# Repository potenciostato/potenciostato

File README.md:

# Potenciostato con comunicación USB sobre LPCXpresso y FreeRTOS

Proyecto Final de la carrera Ingeniería Electrónica de la Universidad Tecnológica Nacional Facultad Regional Avellaneda <br>

El potenciostato es un dispositivo electrónico utilizado en la mayoría de los experimentos electroquímicos.<br>
Es un instrumento capaz de caracterizar la impedancia de una sustancia por medio de la medición de corriente y tensión.<br>

Integrantes del grupo:
- [Arluna, Gustavo Luis](mailto:gustavoarluna@gmail.com)<br>
- [Gómez Caamaño, Axel Lucas](mailto:gomezaxel.lucas@gmail.com)<br>
- [Trinidad, Hernán](mailto:hernantri@gmail.com)<br>

Para más info visitar la [Página Web Oficial](https://potenciostato.github.io) del proyecto

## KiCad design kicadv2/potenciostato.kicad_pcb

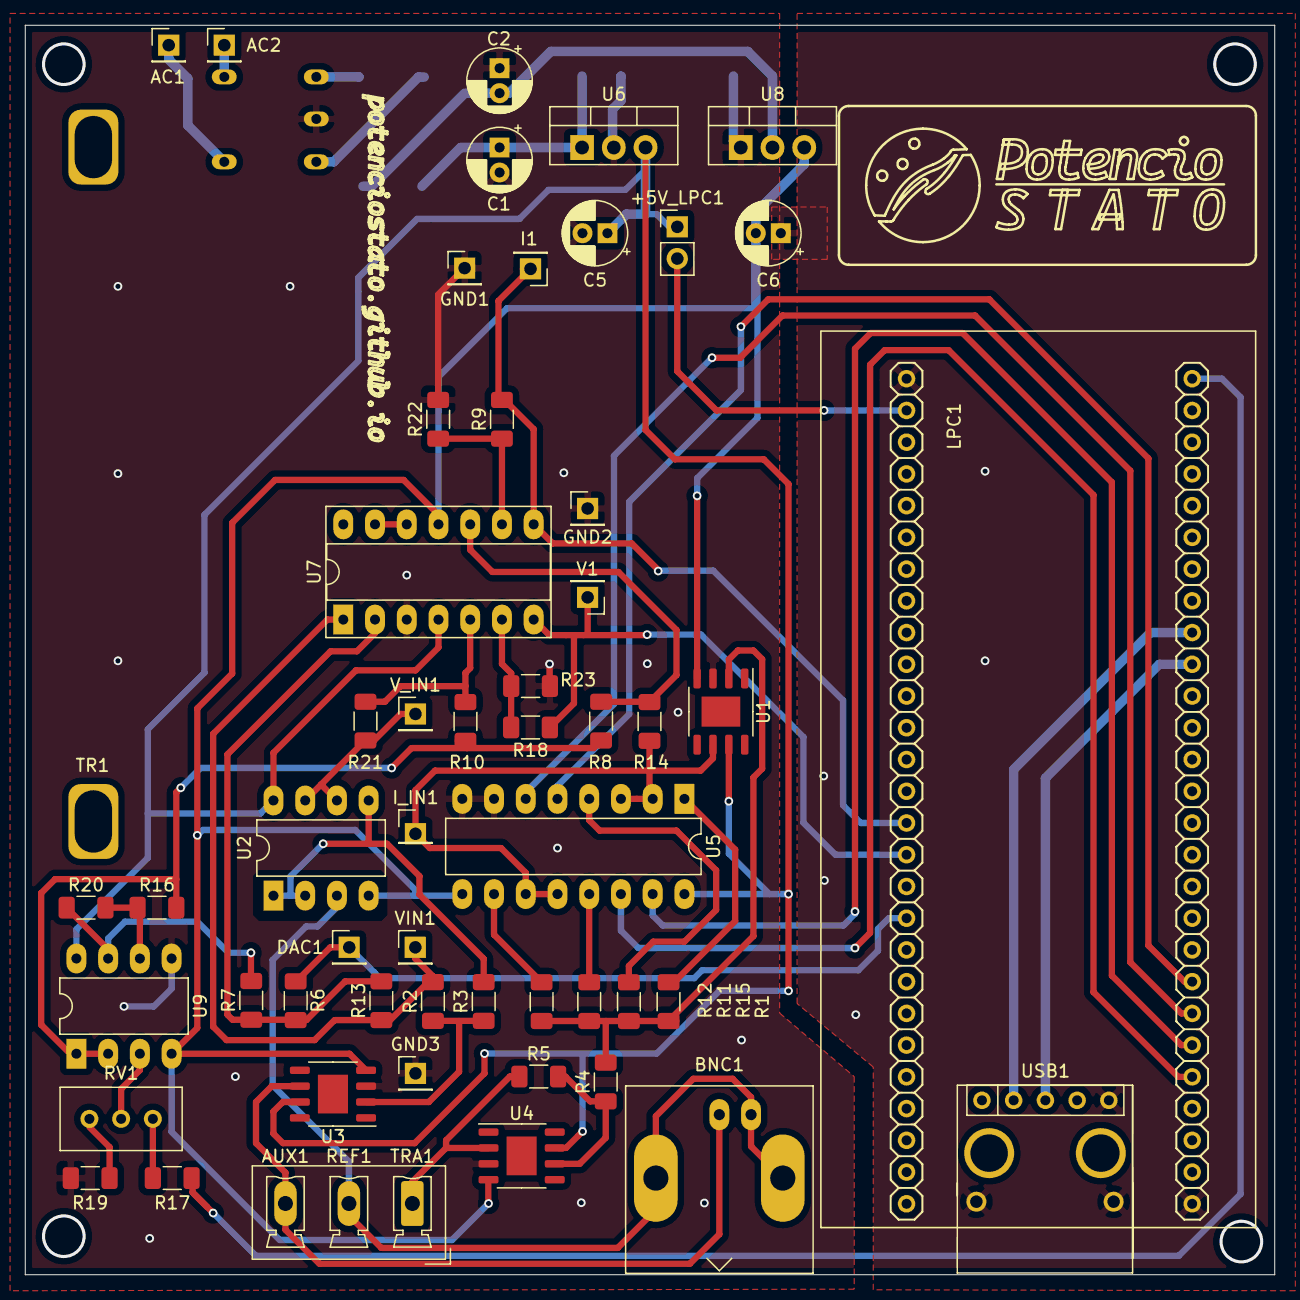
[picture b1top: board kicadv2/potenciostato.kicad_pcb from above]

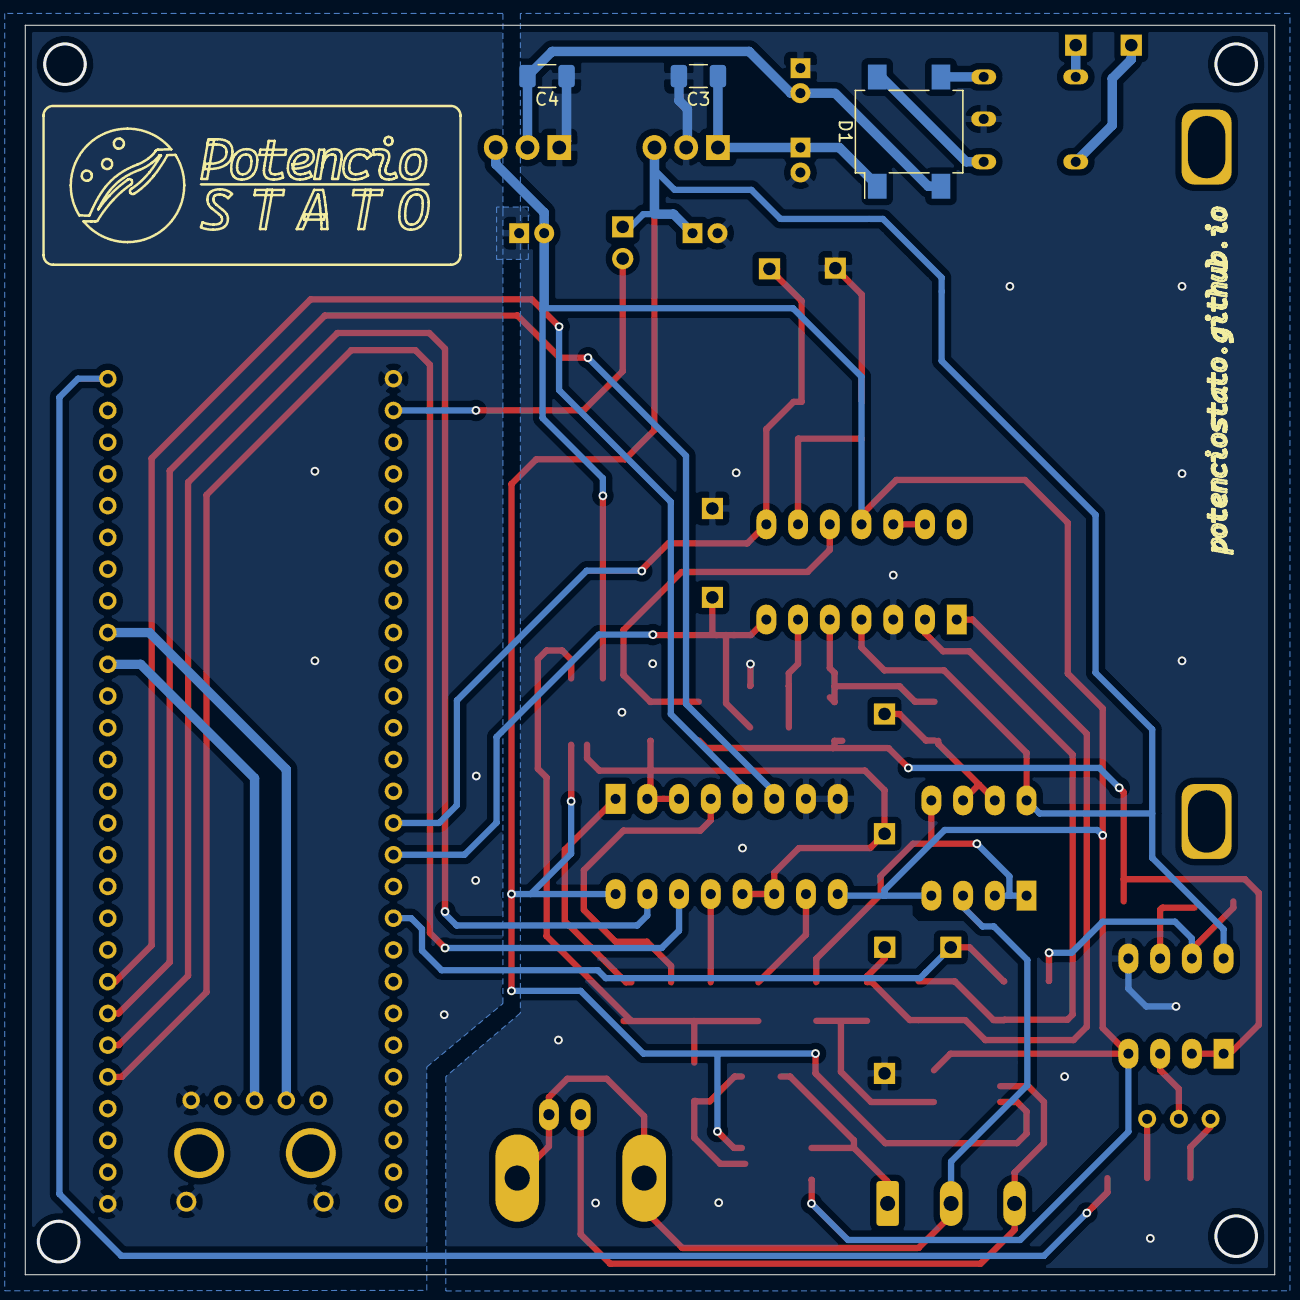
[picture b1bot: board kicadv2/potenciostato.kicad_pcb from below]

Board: 2 copper layers, 100.0 x 100.0 mm, 57 parts (3 on the bottom side), 46 nets.

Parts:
+5V_LPC1: alimentacion_lpc; PinHeader_1x02_P2.54mm_Vertical
AC1: AC1; PinHeader_1x01_P2.54mm_Vertical
AC2: AC2; PinHeader_1x01_P2.54mm_Vertical
AUX1: Conn_01x03_Male; PhoenixContact_MCV_1,5_3-G-5.08_1x03_P5.08mm_Vertical
BNC1: Conn_Coaxial; BNC_Amphenol_B6252HB-NPP3G-50_Horizontal
C1, C2, C5, C6: 10uF; CP_Radial_D5.0mm_P2.00mm
C3, C4: 100nF; C_1206_3216Metric_Pad1.33x1.80mm_HandSolder
D1: D_Bridge_+-AA; Diode_Bridge_Vishay_DFS
DAC1: test_DAC; PinHeader_1x01_P2.54mm_Vertical
GND1, GND2, GND3: test_GND; PinHeader_1x01_P2.54mm_Vertical
I1: test_I; PinHeader_1x01_P2.54mm_Vertical
I_IN1: test_I; PinHeader_1x01_P2.54mm_Vertical
LPC1: LPCXPRESSO_LPC1769
R1: 1K; R_1206_3216Metric_Pad1.30x1.75mm_HandSolder
R2, R3, R11: 100K; R_1206_3216Metric_Pad1.30x1.75mm_HandSolder
R4, R6, R7, R8, R9, R10, R13, R14, R15, R16, R18, R20, R21, R22, R23: 10K; R_1206_3216Metric_Pad1.30x1.75mm_HandSolder
R5: 6K8; R_1206_3216Metric_Pad1.30x1.75mm_HandSolder
R12, R17: 4K7; R_1206_3216Metric_Pad1.30x1.75mm_HandSolder
R19: 5K6; R_1206_3216Metric_Pad1.30x1.75mm_HandSolder
RV1: 10K; Potentiometer_Bourns_3296W_Vertical
TR1: ADT2-71T; Transformador_7.5V
U1, U3, U4: OP77; HSOP-8-1EP_3.9x4.9mm_P1.27mm_EP2.41x3.1mm
U2, U9: TL082; DIP-8_W7.62mm_LongPads
U5: 4316; DIP-16_W7.62mm_LongPads
U6: L7805; TO-220-3_Vertical
U7: TL064; DIP-14_W7.62mm_Socket_LongPads
U8: L7905; TO-220-3_Vertical
USB1: USB_B_Micro; ModuloUSB-Micro
V1: test_V; PinHeader_1x01_P2.54mm_Vertical
VIN1: test_VIN; PinHeader_1x01_P2.54mm_Vertical
V_IN1: test_V; PinHeader_1x01_P2.54mm_Vertical

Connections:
+5V: +5V_LPC1.1, C5.1, U1.7, U2.8, U3.7, U4.7, U5.16, U6.3, U7.4, U9.8
-5V: C6.2, U1.4, U2.4, U3.4, U4.4, U5.9, U7.11, U8.3, U9.4
/salida_dac/3V3: LPC1.28, R17.2
/salida_dac/-VOffset: R7.2, R20.1, U9.7
/salida_dac/I_IN: I_IN1.1, R14.2, U1.6, U5.2, U5.3, U5.11, U5.12
/salida_dac/VIN: R2.2, R13.1, U7.1, VIN1.1
/salida_dac/VOffset: R8.1, R10.1, R16.2, U9.1, U9.2
/salida_dac/V_IN: R21.2, U2.6, U2.7, V_IN1.1
/salida_dac/gan_x0.1: LPC1.49, U5.15
/salida_dac/gan_x1: LPC1.47, U5.5
/salida_dac/gan_x5: LPC1.48, U5.6
/salida_dac/gan_x10: LPC1.50, U5.14
GND: C1.2, C2.1, C3.2, C4.1, C5.2, C6.1, GND1.1, GND2.1, GND3.1, LPC1.1, LPC1.54, R19.1, R22.2, R23.2, TR1.5, U1.3, U3.3, U4.3, U5.7, U5.8, U6.2, U7.3, U8.1, U9.5, USB1.5, USB1.8, USB1.9
unnamed: +5V_LPC1.2, LPC1.2
unnamed: AC1.1, TR1.3
unnamed: AC2.1, TR1.1
unnamed: AUX1.1, R5.1, U4.2
unnamed: AUX1.2, BNC1.2, U2.3
unnamed: AUX1.3, BNC1.1, U3.6
unnamed: C1.1, C3.1, D1.1, U6.1
unnamed: C2.2, C4.2, D1.2, U8.2
unnamed: D1.3, TR1.6
unnamed: D1.4, TR1.4
unnamed: DAC1.1, LPC1.18, R6.2
unnamed: I1.1, LPC1.15, R9.2, U7.8
unnamed: LPC1.16, R18.1, U7.7, V1.1
unnamed: LPC1.36, USB1.2
unnamed: LPC1.37, USB1.3
unnamed: R1.1, R4.2, R11.1, R12.1, R15.1, U1.2
unnamed: R1.2, U5.1
unnamed: R2.1, R3.1, U3.2
unnamed: R3.2, U2.1, U2.2, U2.5
unnamed: R4.1, R5.2, U4.6
unnamed: R10.2, R21.1, U7.5
unnamed: R11.2, U5.13
unnamed: R12.2, U5.10
unnamed: R6.1, R7.1, R13.2, U7.2
unnamed: R8.2, R14.1, U7.10
unnamed: R15.2, U5.4
unnamed: R16.1, R20.2, U9.6
unnamed: R17.1, RV1.1
unnamed: R18.2, R23.1, U7.6
unnamed: R19.2, RV1.3
unnamed: R9.1, R22.1, U7.9
unnamed: RV1.2, U9.3
unnamed: U7.12, U7.13

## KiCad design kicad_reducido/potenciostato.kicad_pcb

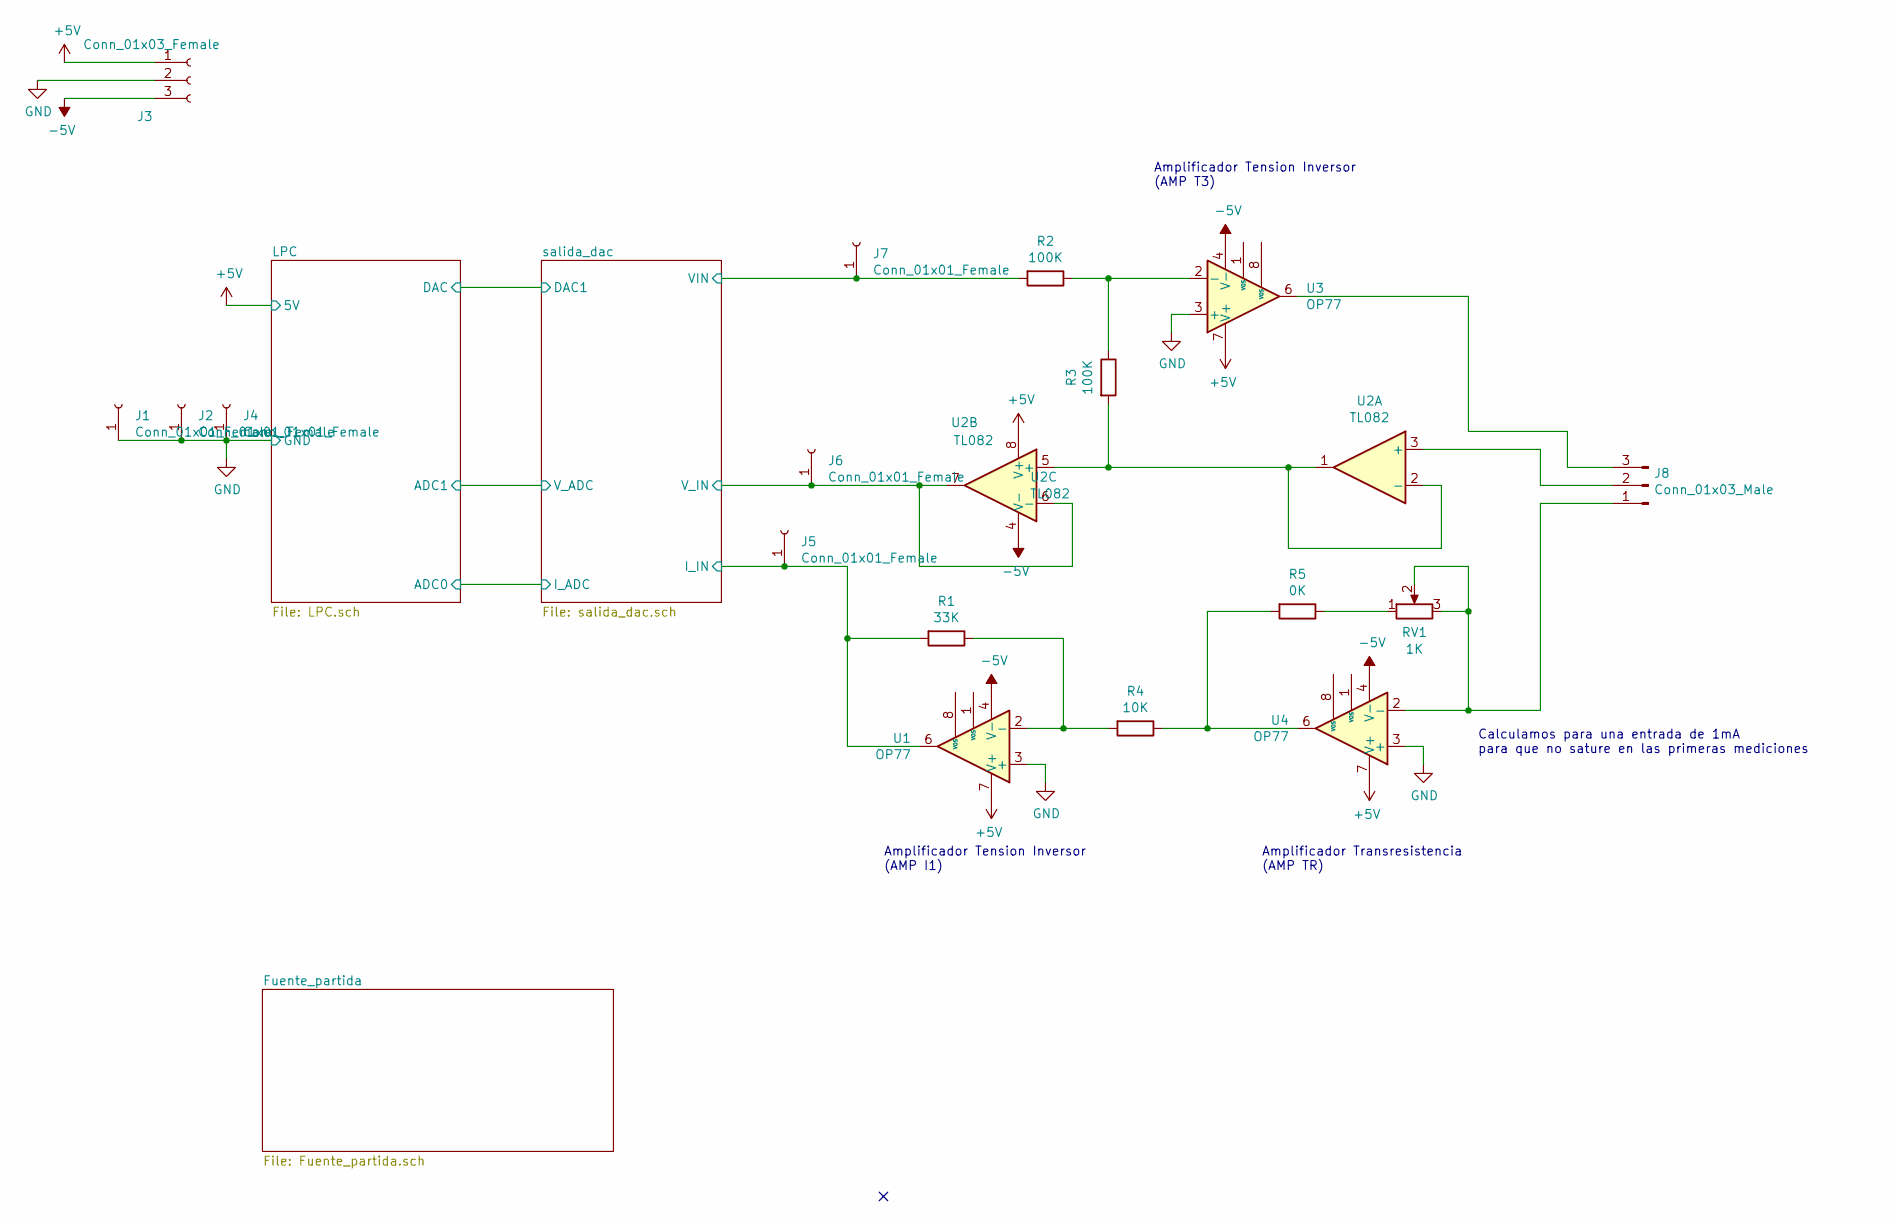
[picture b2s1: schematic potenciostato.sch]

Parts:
J1, J2, J4, J5, J6, J7: Conn_01x01_Female; PinHeader_1x01_P2.54mm_Vertical
J3: Conn_01x03_Female; FanPinHeader_1x03_P2.54mm_Vertical
J8: Conn_01x03_Male; FanPinHeader_1x03_P2.54mm_Vertical
R1: 33K; R_Axial_DIN0207_L6.3mm_D2.5mm_P7.62mm_Horizontal
R2: 100K; R_Axial_DIN0207_L6.3mm_D2.5mm_P7.62mm_Horizontal
R3: 100K; R_Axial_DIN0207_L6.3mm_D2.5mm_P10.16mm_Horizontal
R4: 10K; R_Axial_DIN0207_L6.3mm_D2.5mm_P7.62mm_Horizontal
R5: 0K; R_Axial_DIN0207_L6.3mm_D2.5mm_P7.62mm_Horizontal
RV1: 1K; Potentiometer_Bourns_3266Y_Vertical
U1, U3, U4: OP77; DIP-8_W7.62mm_LongPads
U2: TL082; DIP-8_W7.62mm_LongPads

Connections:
+5V: J3.1, U1.7 (V+), U2.8 (V+), U3.7 (V+), U4.7 (V+); also elsewhere on the board
-5V: J3.3, U1.4 (V-), U2.4 (V-), U3.4 (V-), U4.4 (V-); also elsewhere on the board
/salida_dac/I_IN: J5.1, R1.2, U1.6; also elsewhere on the board
/salida_dac/VIN: J7.1, R2.2; also elsewhere on the board
/salida_dac/V_IN: J6.1, U2.6 (-), U2.7; also elsewhere on the board
GND: J1.1, J2.1, J3.2, J4.1, U1.3 (+), U3.3 (+), U4.3 (+); also elsewhere on the board
unnamed: J8.1, RV1.2, RV1.3, U4.2 (-)
unnamed: J8.3, U3.6
unnamed: R1.1, R4.2, U1.2 (-)
unnamed: R2.1, R3.1, U3.2 (-)
unnamed: R3.2, U2.1, U2.2 (-), U2.5 (+)
unnamed: R4.1, R5.2, U4.6
unnamed: R5.1, RV1.1

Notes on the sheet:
Amplificador Tension Inversor (AMP I1)
Amplificador Tension Inversor (AMP T3)
Amplificador Transresistencia (AMP TR)
Calculamos para una entrada de 1mA para que no sature en las primeras mediciones

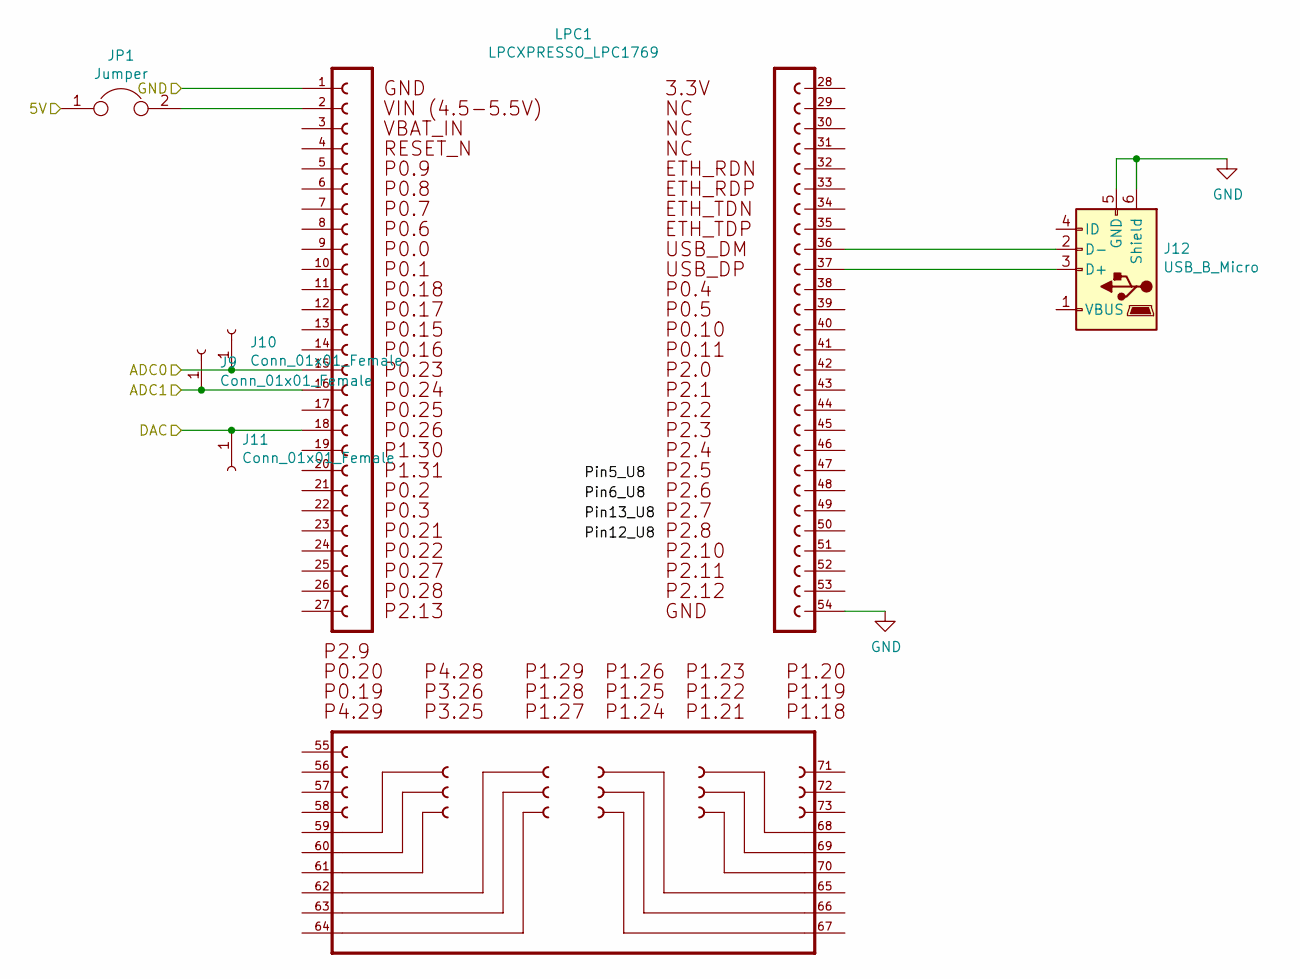
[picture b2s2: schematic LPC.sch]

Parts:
J9, J10, J11: Conn_01x01_Female; PinHeader_1x01_P2.54mm_Vertical
J12: USB_B_Micro; USB_Mini-B_Wuerth_65100516121_Horizontal
JP1: Jumper; PinHeader_1x02_P2.54mm_Vertical
LPC1: LPCXPRESSO_LPC1769

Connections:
+5V: JP1.1; also elsewhere on the board
/LPC/ADC0: J10.1, LPC1.15; also elsewhere on the board
/LPC/ADC1: J9.1, LPC1.16; also elsewhere on the board
/LPC/DAC: J11.1, LPC1.18; also elsewhere on the board
GND: J12.5 (GND), J12.6 (Shield), LPC1.1, LPC1.54; also elsewhere on the board
unnamed: J12.2 (D-), LPC1.36
unnamed: J12.3 (D+), LPC1.37
unnamed: JP1.2, LPC1.2

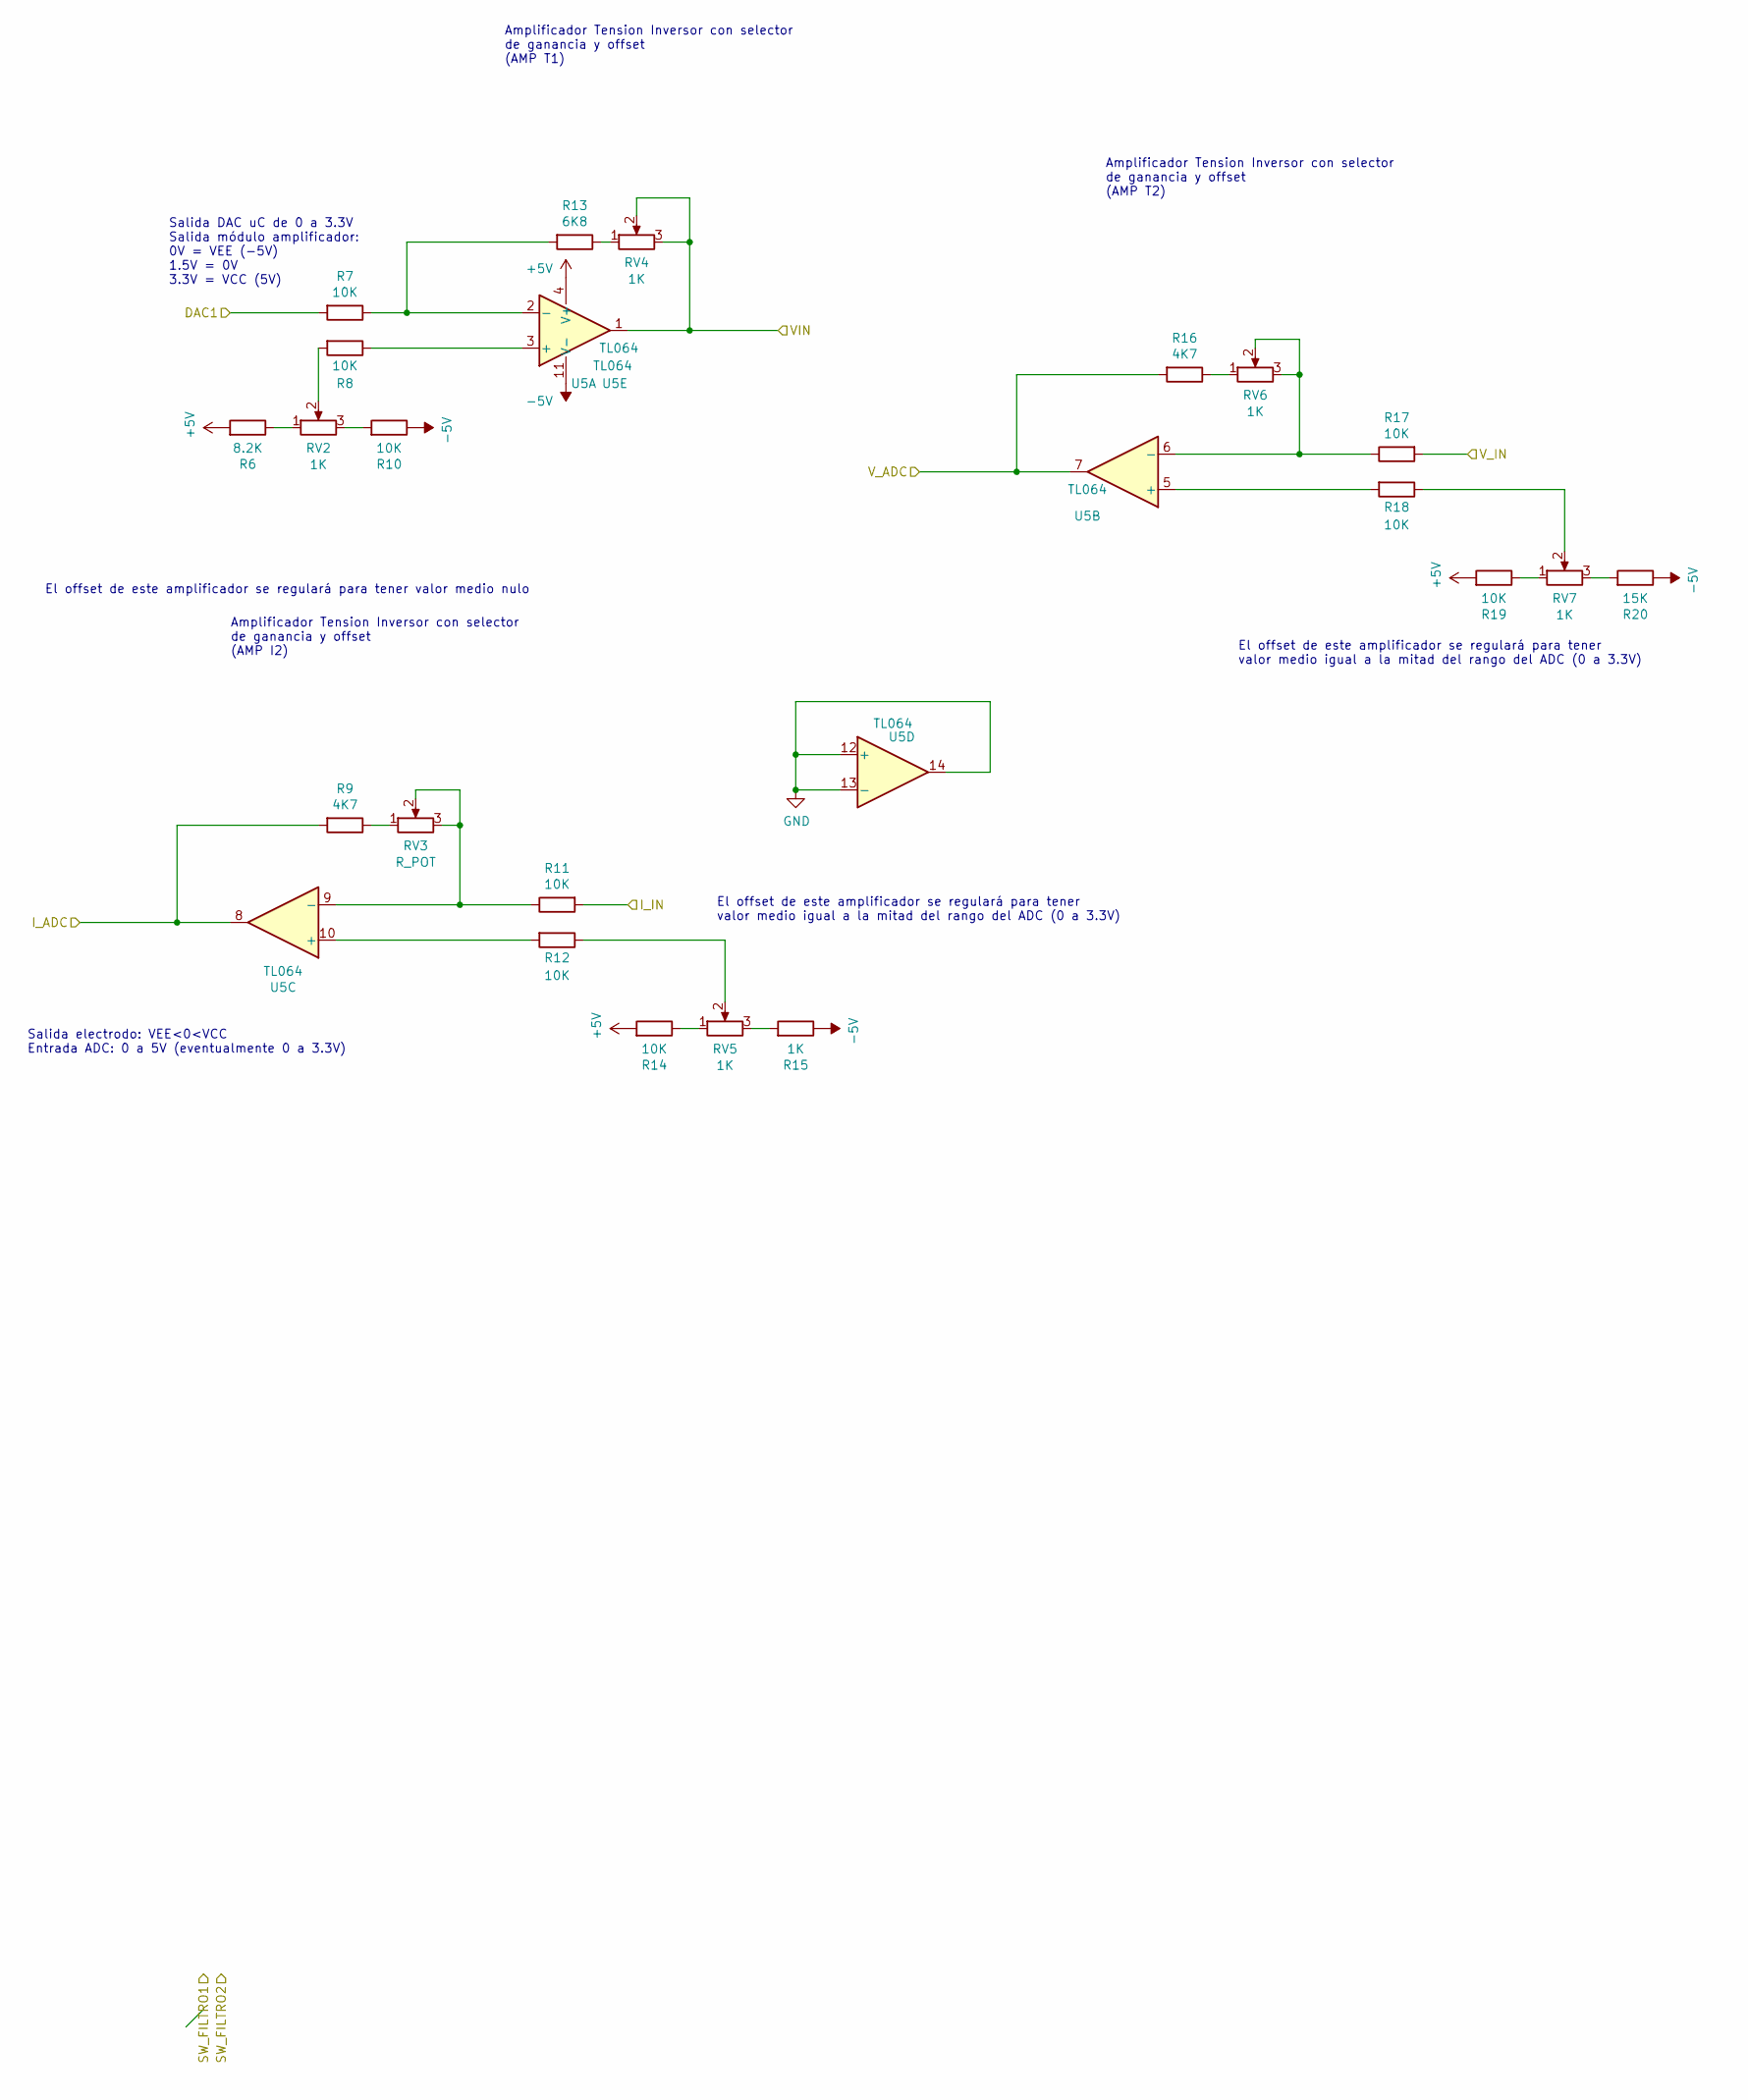
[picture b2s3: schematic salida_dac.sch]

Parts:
R6: 8.2K; R_Axial_DIN0207_L6.3mm_D2.5mm_P7.62mm_Horizontal
R7, R10, R11, R12, R14, R17, R18, R19: 10K; R_Axial_DIN0207_L6.3mm_D2.5mm_P7.62mm_Horizontal
R8: 10K; R_Axial_DIN0207_L6.3mm_D2.5mm_P10.16mm_Horizontal
R9, R16: 4K7; R_Axial_DIN0207_L6.3mm_D2.5mm_P7.62mm_Horizontal
R13: 6K8; R_Axial_DIN0207_L6.3mm_D2.5mm_P7.62mm_Horizontal
R15: 1K; R_Axial_DIN0207_L6.3mm_D2.5mm_P7.62mm_Horizontal
R20: 15K; R_Axial_DIN0207_L6.3mm_D2.5mm_P7.62mm_Horizontal
RV2, RV4, RV5, RV6, RV7: 1K; Potentiometer_Bourns_3266Y_Vertical
RV3: R_POT; Potentiometer_Bourns_3266Y_Vertical
U5: TL064; DIP-14_W7.62mm_Socket_LongPads

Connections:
+5V: R6.2, R14.2, R19.2, U5.4 (V+); also elsewhere on the board
-5V: R10.1, R15.1, R20.1, U5.11 (V-); also elsewhere on the board
/LPC/ADC0: R9.2, U5.8; also elsewhere on the board
/LPC/ADC1: R16.2, U5.7; also elsewhere on the board
/LPC/DAC: R7.2; also elsewhere on the board
/salida_dac/I_IN: R11.2; also elsewhere on the board
/salida_dac/VIN: RV4.2, RV4.3, U5.1; also elsewhere on the board
/salida_dac/V_IN: R17.2; also elsewhere on the board
GND: U5.12 (+), U5.13 (-), U5.14; also elsewhere on the board
unnamed: R6.1, RV2.1
unnamed: R8.1, U5.3 (+)
unnamed: R8.2, RV2.2
unnamed: R9.1, RV3.1
unnamed: R10.2, RV2.3
unnamed: R11.1, RV3.2, RV3.3, U5.9 (-)
unnamed: R12.1, RV5.2
unnamed: R12.2, U5.10 (+)
unnamed: R13.1, RV4.1
unnamed: R7.1, R13.2, U5.2 (-)
unnamed: R14.1, RV5.1
unnamed: R15.2, RV5.3
unnamed: R16.1, RV6.1
unnamed: R17.1, RV6.2, RV6.3, U5.6 (-)
unnamed: R18.1, RV7.2
unnamed: R18.2, U5.5 (+)
unnamed: R19.1, RV7.1
unnamed: R20.2, RV7.3

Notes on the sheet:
Salida DAC uC de 0 a 3.3V Salida módulo amplificador: 0V = VEE (-5V) 1.5V = 0V 3.3V = VCC (5V)
Salida electrodo: VEE<0<VCC Entrada ADC: 0 a 5V (eventualmente 0 a 3.3V)
Amplificador Tension Inversor con selector de ganancia y offset (AMP T1)
Amplificador Tension Inversor con selector de ganancia y offset (AMP T2)
El offset de este amplificador se regulará para tener valor medio nulo
El offset de este amplificador se regulará para tener valor medio igual a la mitad del rango del ADC (0 a 3.3V)
Amplificador Tension Inversor con selector de ganancia y offset (AMP I2)

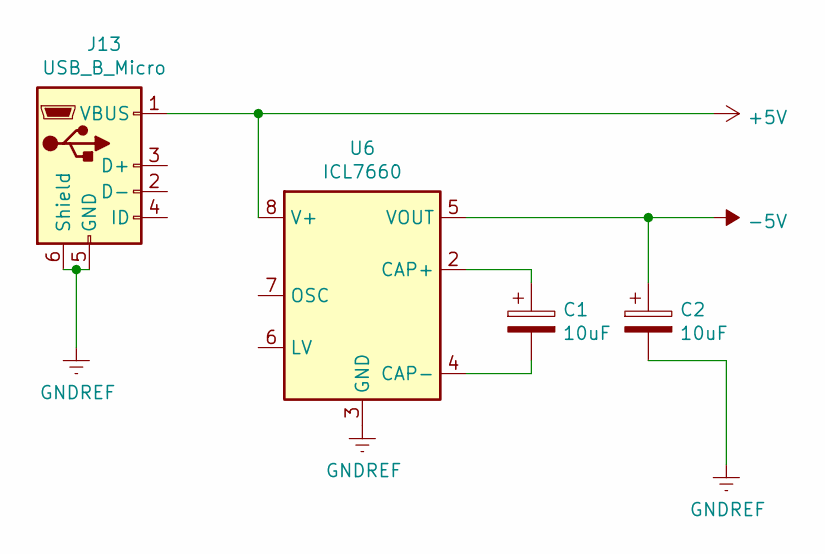
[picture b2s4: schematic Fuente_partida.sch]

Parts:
C1, C2: 10uF
J13: USB_B_Micro
U6: ICL7660

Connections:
unnamed: C1.1, U6.2 (CAP+)
unnamed: C1.2, U6.4 (CAP-)
unnamed: C2.1, U6.5 (VOUT)
unnamed: C2.2, J13.5 (GND), J13.6 (Shield), U6.3 (GND)
unnamed: J13.1 (VBUS), U6.8 (V+)

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
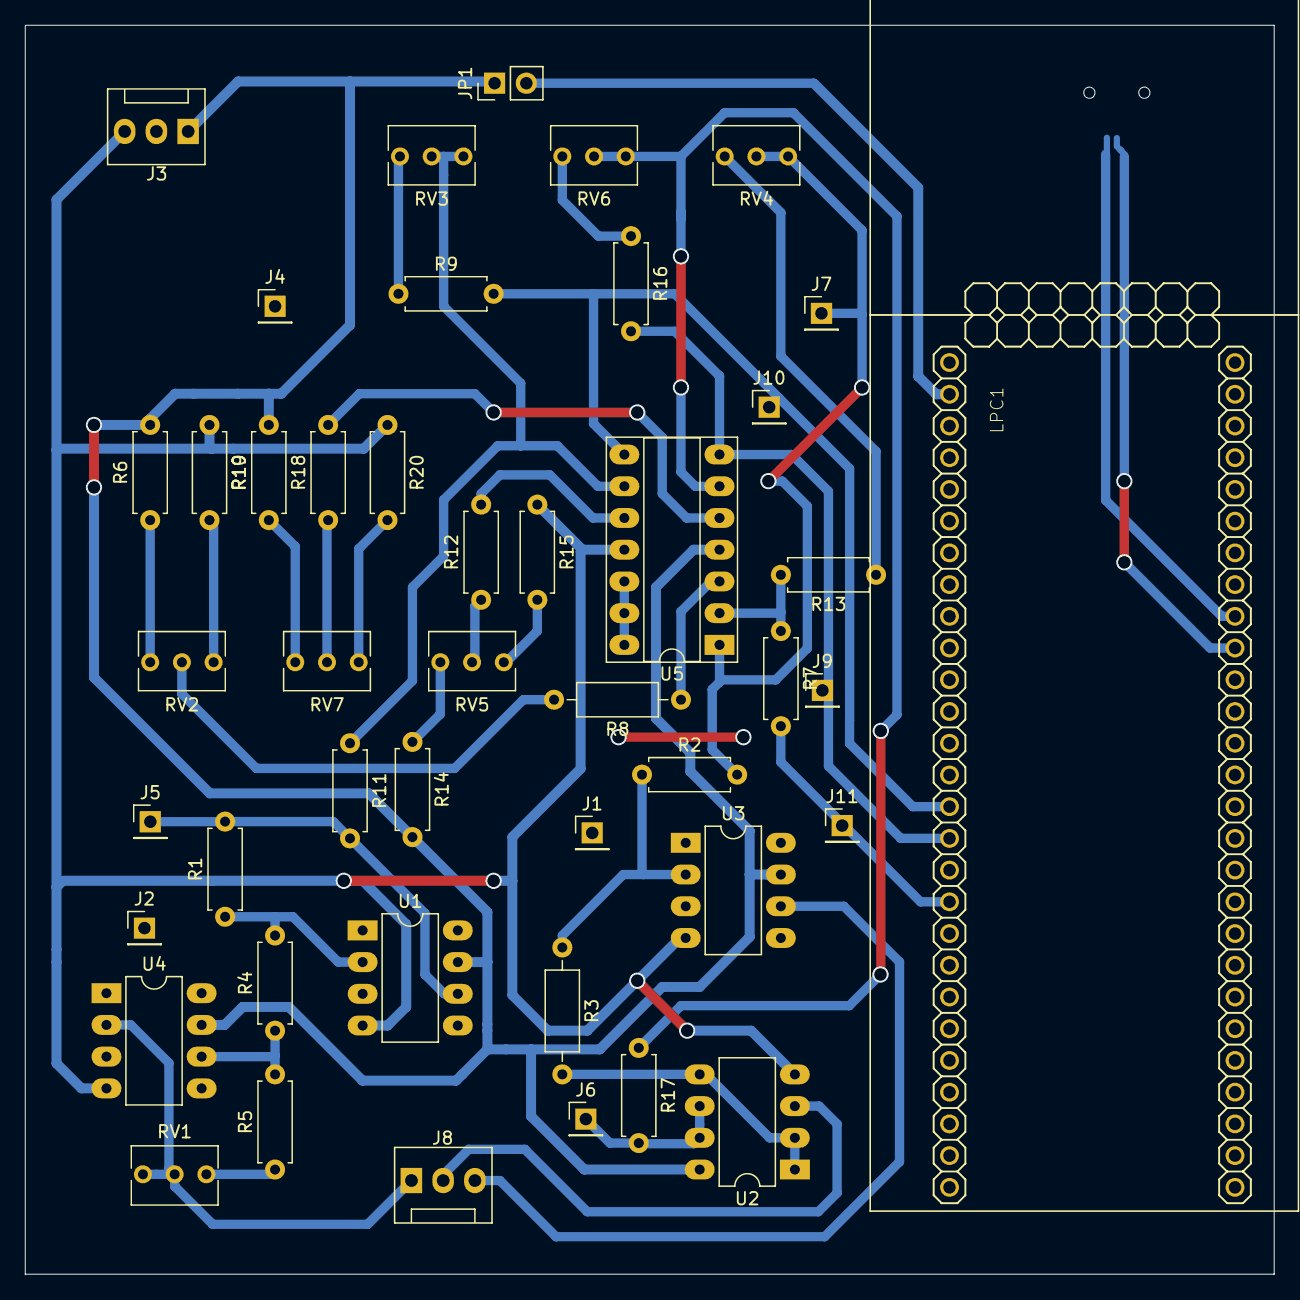
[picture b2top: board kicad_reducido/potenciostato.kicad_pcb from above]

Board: 2 copper layers, 100.0 x 100.0 mm, 46 parts (1 on the bottom side), 37 nets.

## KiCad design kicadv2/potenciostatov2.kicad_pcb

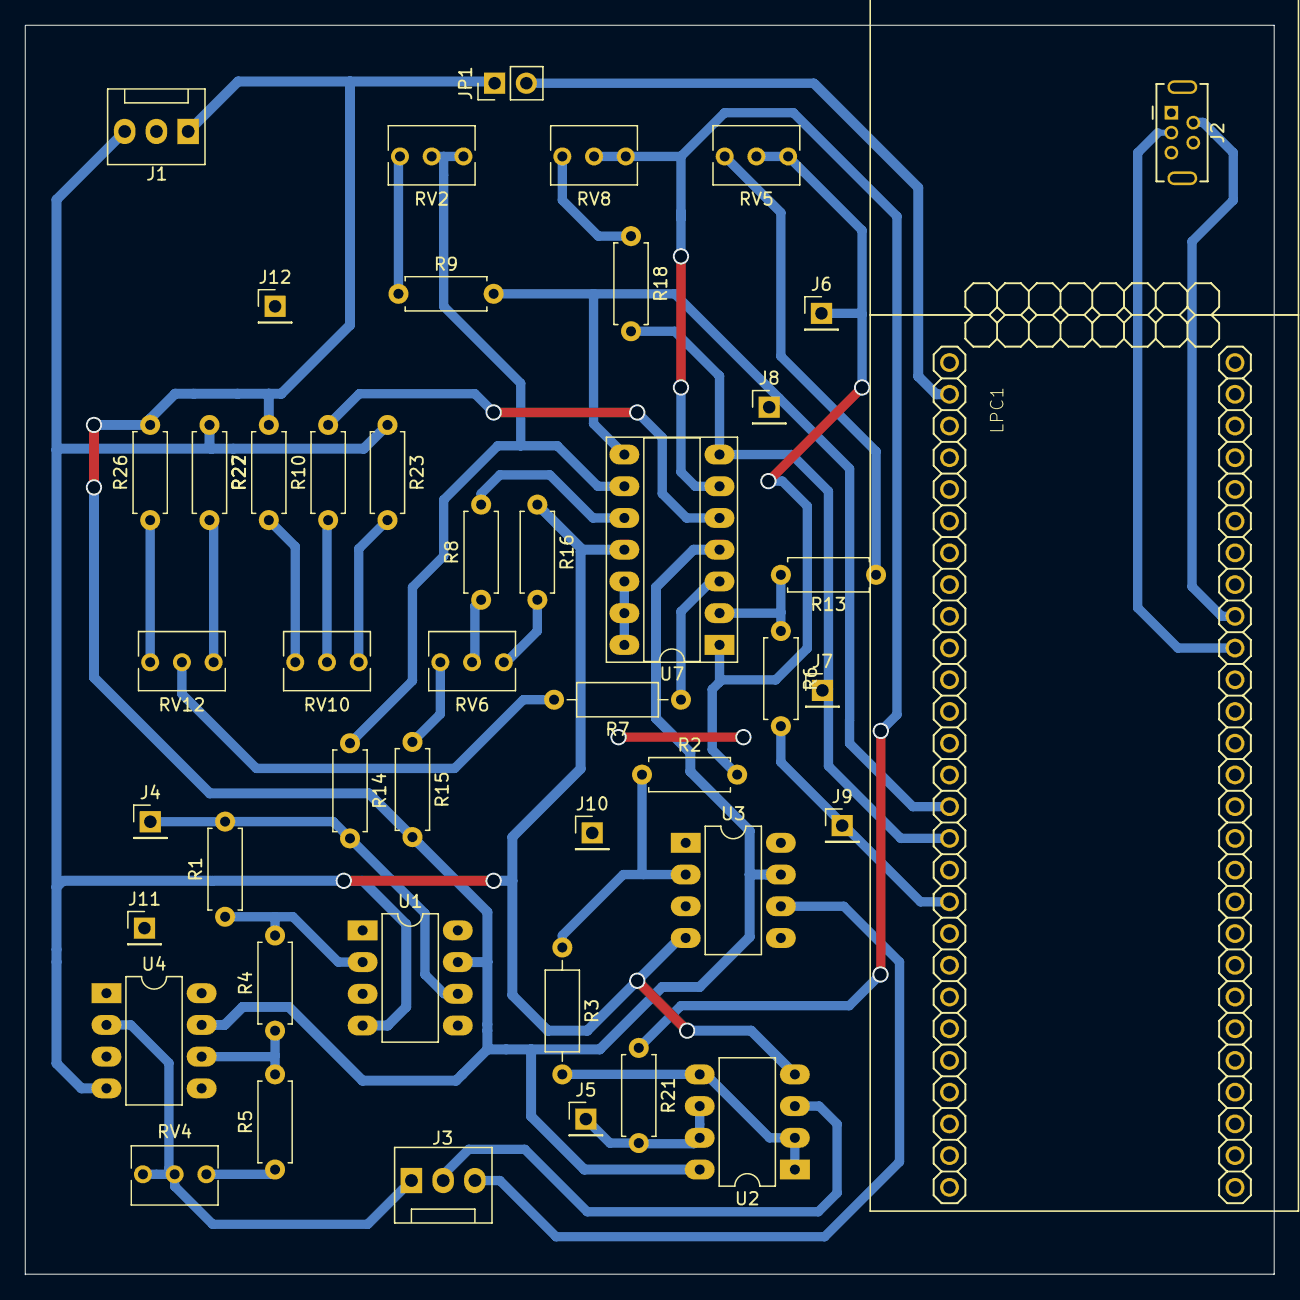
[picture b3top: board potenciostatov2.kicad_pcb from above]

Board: 2 copper layers, 100.0 x 100.0 mm, 46 parts (0 on the bottom side), 38 nets.

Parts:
J1: Conn_01x03_Female; FanPinHeader_1x03_P2.54mm_Vertical
J2: USB_B_Micro; USB_Mini-B_Tensility_54-00023_Vertical
J3: Conn_01x03_Male; FanPinHeader_1x03_P2.54mm_Vertical
J4, J5, J6, J7, J8, J9, J10, J11, J12: Conn_01x01_Female; PinHeader_1x01_P2.54mm_Vertical
JP1: Jumper; PinHeader_1x02_P2.54mm_Vertical
LPC1: LPCXPRESSO_LPC1769
R1, R23: 15K; R_Axial_DIN0207_L6.3mm_D2.5mm_P7.62mm_Horizontal
R2: 100K; R_Axial_DIN0207_L6.3mm_D2.5mm_P7.62mm_Horizontal
R3: 100K; R_Axial_DIN0207_L6.3mm_D2.5mm_P10.16mm_Horizontal
R4, R6, R8, R10, R14, R16, R21, R27: 1K; R_Axial_DIN0207_L6.3mm_D2.5mm_P7.62mm_Horizontal
R5: 1M; R_Axial_DIN0207_L6.3mm_D2.5mm_P7.62mm_Horizontal
R7: 1K; R_Axial_DIN0207_L6.3mm_D2.5mm_P10.16mm_Horizontal
R9, R13, R18: 4K7; R_Axial_DIN0207_L6.3mm_D2.5mm_P7.62mm_Horizontal
R15, R22, R26: 10K; R_Axial_DIN0207_L6.3mm_D2.5mm_P7.62mm_Horizontal
RV2, RV5: R_POT; Potentiometer_Bourns_3266Y_Vertical
RV4, RV6, RV8, RV10, RV12: 1K; Potentiometer_Bourns_3266Y_Vertical
U1, U3, U4: OP77; DIP-8_W7.62mm_LongPads
U2: TL082; DIP-8_W7.62mm_LongPads
U7: TL064; DIP-14_W7.62mm_Socket_LongPads

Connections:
+5V: J1.1, JP1.1, R15.2, R22.2, R26.2, U1.7, U2.8, U3.7, U4.7, U7.4
-5V: J1.3, R16.1, R23.1, R27.1, U1.4, U2.4, U3.4, U4.4, U7.11
/LPC/ADC0: J8.1, LPC1.15, R9.2, U7.8
/LPC/ADC1: J7.1, LPC1.16, R18.2, U7.7
/LPC/DAC: J9.1, LPC1.18, R6.2
/salida_dac/I_IN: J4.1, R1.2, R14.2, U1.6
/salida_dac/VIN: J6.1, R2.2, RV5.2, RV5.3, U7.1
/salida_dac/V_IN: J5.1, R21.2, U2.6, U2.7
GND: J1.2, J2.5, J2.6, J10.1, J11.1, J12.1, LPC1.1, LPC1.54, U1.3, U3.3, U4.3, U7.12, U7.13, U7.14
unnamed: J2.2, LPC1.36
unnamed: J2.3, LPC1.37
unnamed: J3.1, RV4.2, RV4.3, U4.2
unnamed: J3.2, U2.3
unnamed: J3.3, U3.6
unnamed: JP1.2, LPC1.2
unnamed: R1.1, R4.2, U1.2
unnamed: R2.1, R3.1, U3.2
unnamed: R3.2, U2.1, U2.2, U2.5
unnamed: R4.1, R5.2, U4.6
unnamed: R5.1, RV4.1
unnamed: R7.1, U7.3
unnamed: R7.2, RV12.2
unnamed: R8.1, RV6.2
unnamed: R8.2, U7.10
unnamed: R9.1, RV2.1
unnamed: R10.1, RV10.2
unnamed: R10.2, U7.5
unnamed: R13.1, RV5.1
unnamed: R6.1, R13.2, U7.2
unnamed: R14.1, RV2.2, RV2.3, U7.9
unnamed: R15.1, RV6.1
unnamed: R16.2, RV6.3
unnamed: R18.1, RV8.1
unnamed: R21.1, RV8.2, RV8.3, U7.6
unnamed: R22.1, RV10.1
unnamed: R23.2, RV10.3
unnamed: R26.1, RV12.1
unnamed: R27.2, RV12.3
